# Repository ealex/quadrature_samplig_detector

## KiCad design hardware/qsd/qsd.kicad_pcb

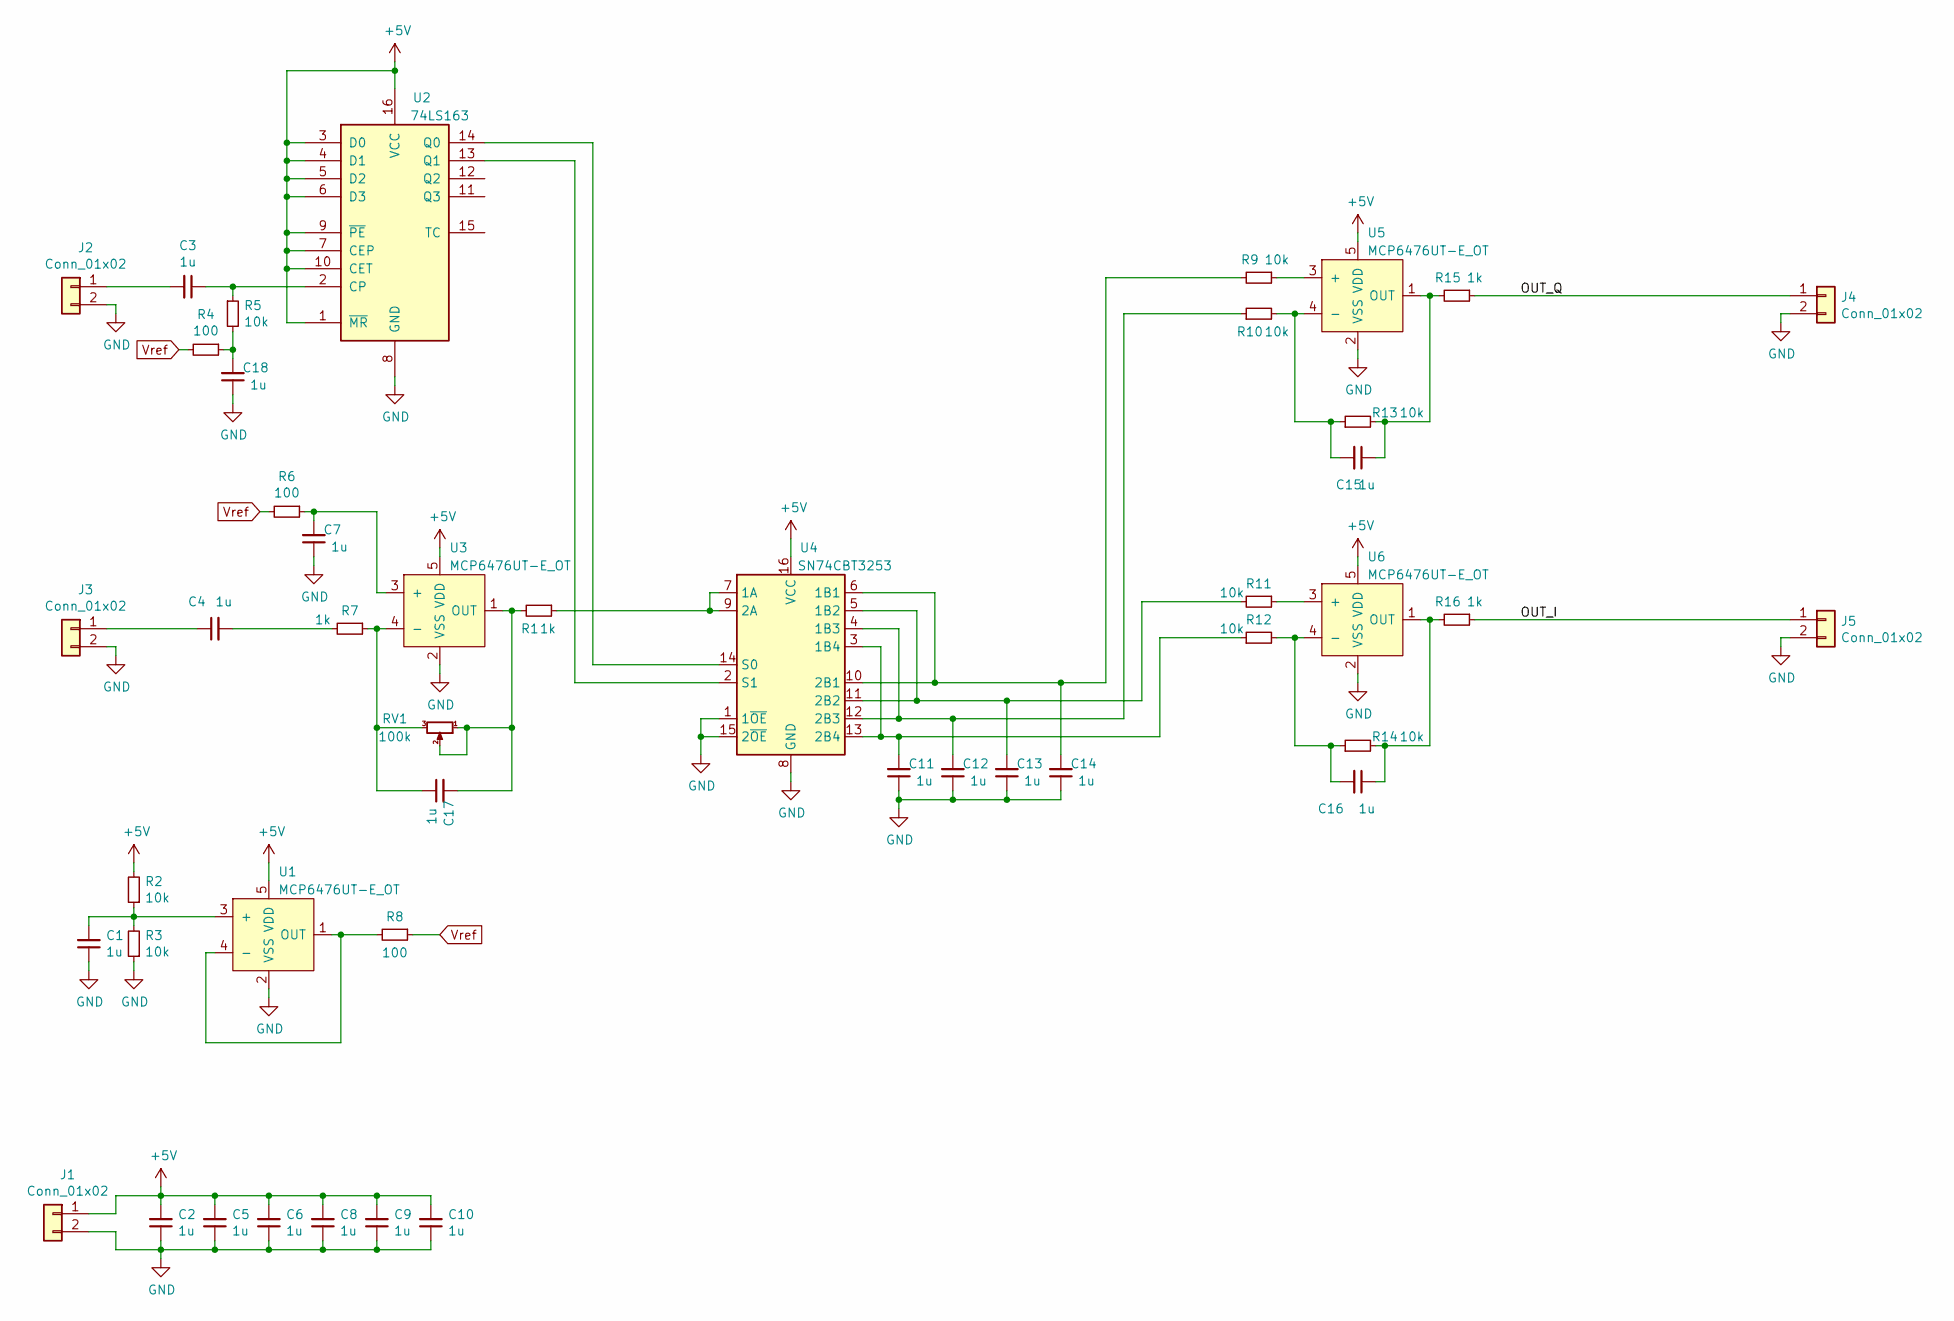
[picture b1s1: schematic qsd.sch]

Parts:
C1, C2, C3, C4, C5, C6, C7, C8, C9, C10, C11, C12, C13, C14, C15, C16, C17, C18: 1u; C_1206_3216Metric
J1, J2, J3, J4, J5: Conn_01x02; PinHeader_1x02_P2.54mm_Vertical
R1, R7, R15, R16: 1k; R_1206_3216Metric
R2, R3, R5, R9, R10, R11, R12, R13, R14: 10k; R_1206_3216Metric
R4, R6, R8: 100; R_1206_3216Metric
RV1: 100k; PinHeader_1x03_P2.54mm_Vertical
U1, U3, U5, U6: MCP6476UT-E_OT; SOT-23-5_HandSoldering
U2: 74LS163; SOIC-16_3.9x9.9mm_P1.27mm
U4: SN74CBT3253; TSSOP-16_4.4x5mm_P0.65mm

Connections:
+5V: C2.2, C5.2, C6.2, C8.2, C9.2, C10.2, J1.1, R2.2, U1.5 (VDD), U2.1 (~MR), U2.3 (D0), U2.4 (D1), U2.5 (D2), U2.6 (D3), U2.7 (CEP), U2.9 (~PE), U2.10 (CET), U2.16 (VCC), U3.5 (VDD), U4.16 (VCC), U5.5 (VDD), U6.5 (VDD)
/OUT_I: J5.1, R16.1
/OUT_Q: J4.1, R15.1
GND: C1.1, C2.1, C5.1, C6.1, C7.1, C8.1, C9.1, C10.1, C11.1, C12.1, C13.1, C14.1, C18.1, J1.2, J2.2, J3.2, J4.2, J5.2, R3.1, U1.2 (VSS), U2.8 (GND), U3.2 (VSS), U4.1 (1~OE), U4.8 (GND), U4.15 (2~OE), U5.2 (VSS), U6.2 (VSS)
unnamed: C1.2, R2.1, R3.2, U1.3 (+)
unnamed: C3.1, R5.1, U2.2 (CP)
unnamed: C3.2, J2.1
unnamed: C4.1, J3.1
unnamed: C4.2, R7.2
unnamed: C7.2, R6.1, U3.3 (+)
unnamed: C11.2, R12.1, U4.3 (1B4), U4.13 (2B4)
unnamed: C12.2, R10.1, U4.4 (1B3), U4.12 (2B3)
unnamed: C13.2, R11.2, U4.5 (1B2), U4.11 (2B2)
unnamed: C14.2, R9.2, U4.6 (1B1), U4.10 (2B1)
unnamed: C15.1, R13.2, R15.2, U5.1 (OUT)
unnamed: C15.2, R10.2, R13.1, U5.4 (-)
unnamed: C16.1, R14.2, R16.2, U6.1 (OUT)
unnamed: C16.2, R12.2, R14.1, U6.4 (-)
unnamed: C17.1, R7.1, RV1.3, U3.4 (-)
unnamed: C17.2, R1.2, RV1.1, RV1.2, U3.1 (OUT)
unnamed: C18.2, R4.1, R5.2
unnamed: R1.1, U4.7 (1A), U4.9 (2A)
unnamed: R8.2, U1.1 (OUT), U1.4 (-)
unnamed: R9.1, U5.3 (+)
unnamed: R11.1, U6.3 (+)
unnamed: U2.13 (Q1), U4.2 (S1)
unnamed: U2.14 (Q0), U4.14 (S0)
Vref: R4.2, R6.2, R8.1

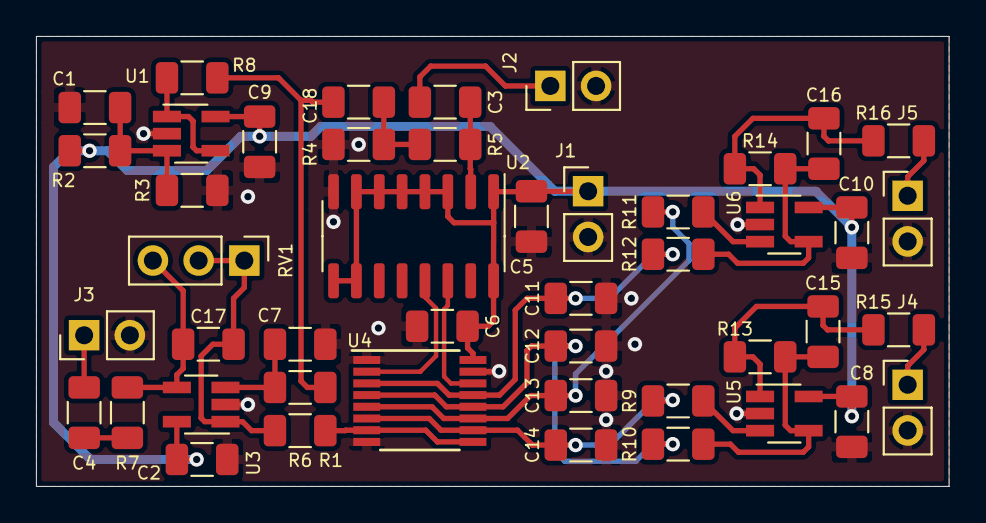
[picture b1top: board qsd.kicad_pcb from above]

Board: 2 copper layers, 50.7 x 25.0 mm, 46 parts (0 on the bottom side), 28 nets.

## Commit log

2022-01-19 add parts datasheet, add source material
2022-01-19 add schematics
2022-01-19 extra docs
